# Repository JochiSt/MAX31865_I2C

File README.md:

# MAX31865_I2C
SPI to I2C bridge fo iInterfacing the MAX31865 via I2C

# Board / Hardware
The hardware has the same size as the Adafriut MAX31865 module. Also the SPI
connection is at the same position. This allows mounting the module on the back
of the MAX31865 module.

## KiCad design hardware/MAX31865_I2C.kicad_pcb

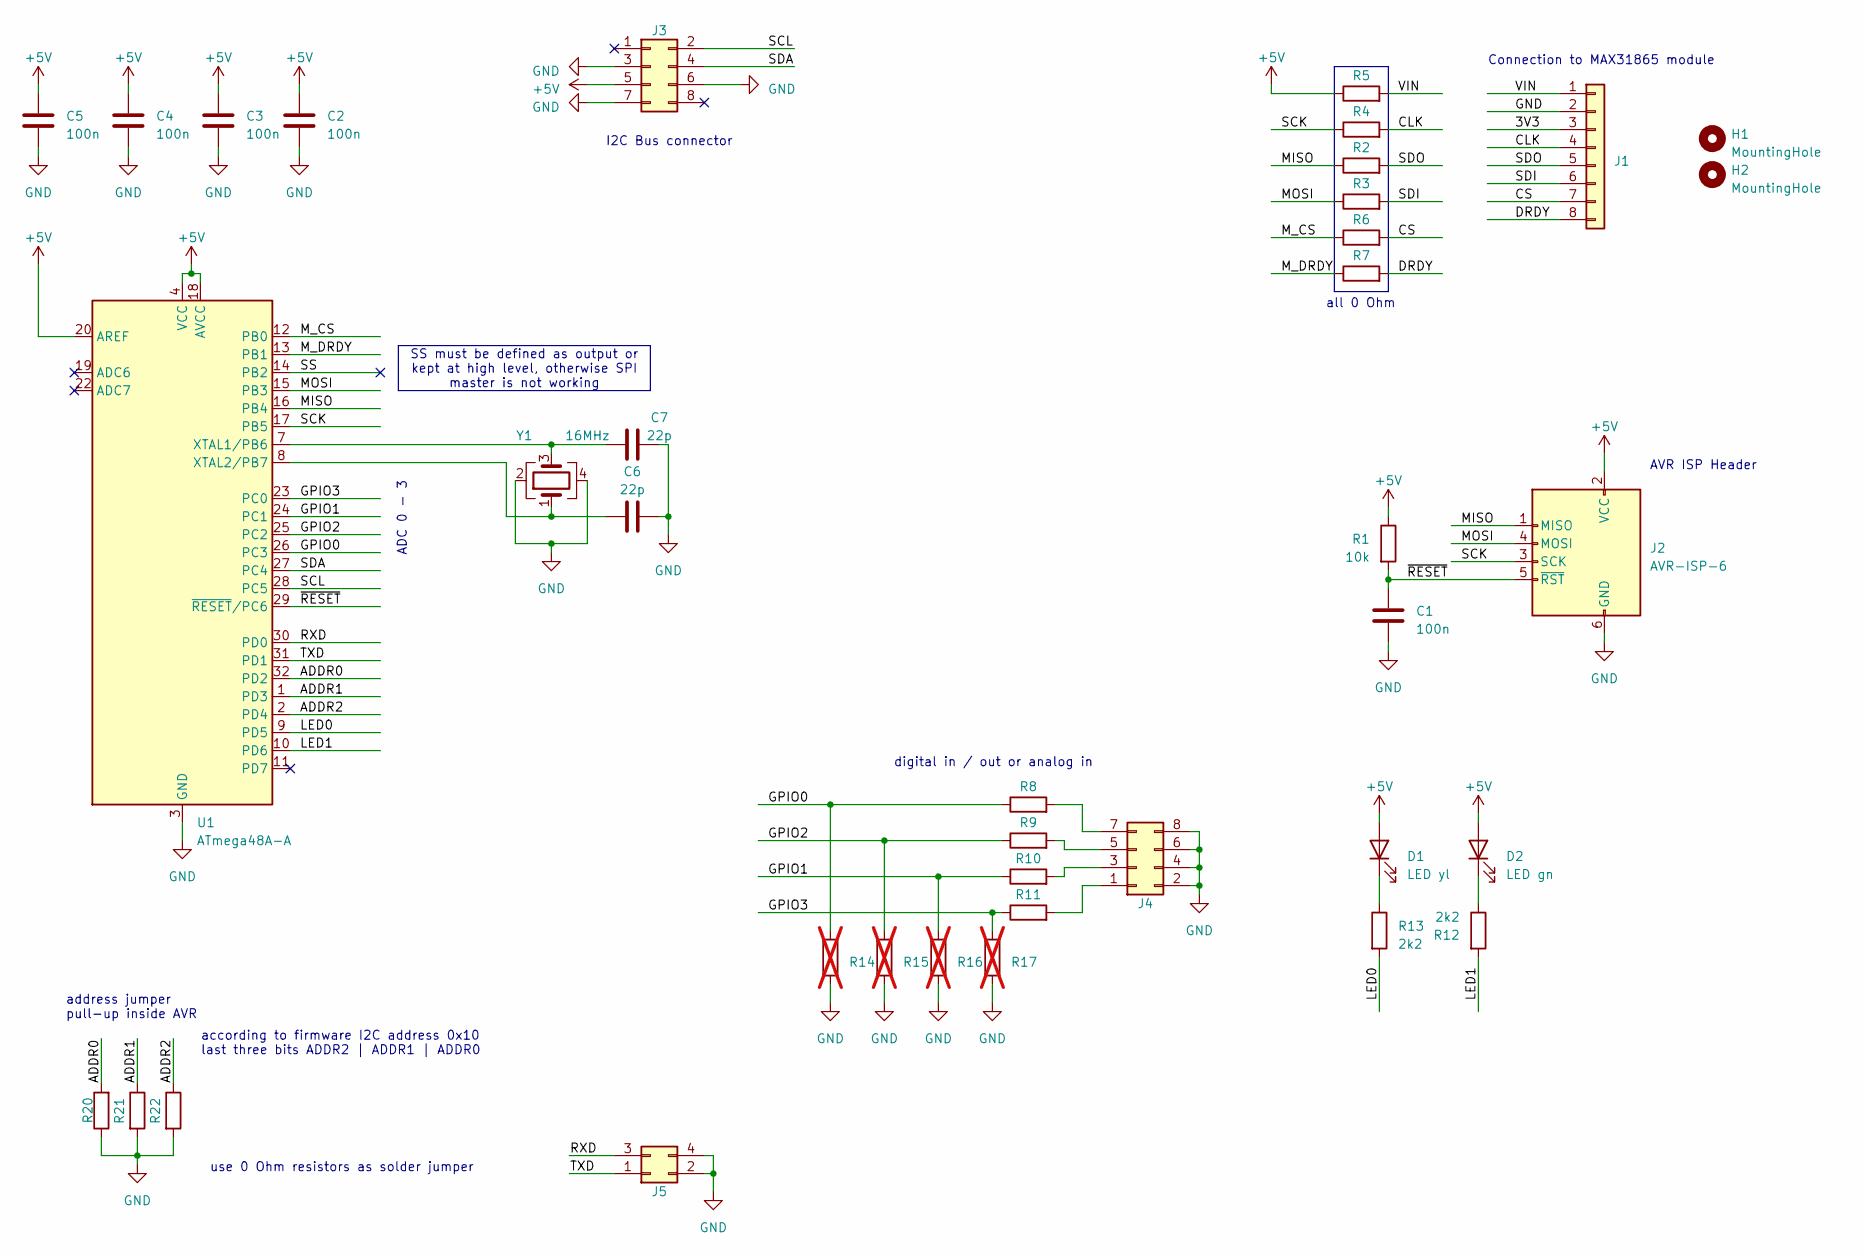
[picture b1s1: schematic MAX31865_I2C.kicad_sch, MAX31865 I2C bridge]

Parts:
C1, C2, C3, C4, C5: 100n; C_0603_1608Metric
C6, C7: 22p; C_0603_1608Metric
D1: LED yl; LED_0603_1608Metric
D2: LED gn; LED_0603_1608Metric
H1, H2: MountingHole; MountingHole_2.7mm
J1: Conn_01x08; PinSocket_1x08_P2.54mm_Vertical
J2: AVR-ISP-6; PinHeader_2x03_P2.54mm_Edge
J3, J4: Conn_02x04_Odd_Even; PinHeader_2x04_P2.54mm_Edge
J5: Conn_02x02_Odd_Even; PinHeader_2x02_P2.54mm_Edge
R1: 10k; R_0603_1608Metric
R2, R3, R4, R5, R6, R7, R8, R9, R10, R11: 0; R_0603_1608Metric
R12, R13: 2k2; R_0603_1608Metric
R14, R15, R16, R17: R_0603_1608Metric; not fitted
R20, R21, R22: R_0603_1608Metric
U1: ATmega48A-A; TQFP-32_7x7mm_P0.8mm
Y1: 16MHz; Crystal_SMD_EuroQuartz_MQ-4Pin_7.0x5.0mm

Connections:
+5V: C2.1, C3.1, C4.1, C5.1, D1.2 (A), D2.2 (A), J2.2 (VCC), J3.5, R1.1, R5.1, U1.4 (VCC), U1.6 (VCC), U1.18 (AVCC), U1.20 (AREF)
/3V3: J1.3
/ADDR0: R20.2, U1.32 (PD2)
/ADDR1: R21.1, U1.1 (PD3)
/ADDR2: R22.1, U1.2 (PD4)
/CLK: J1.4, R4.2
/CS: J1.7, R6.2
/DRDY: J1.8, R7.2
/GPIO0: R8.1, R14.2, U1.26 (PC3)
/GPIO1: R10.1, R16.2, U1.24 (PC1)
/GPIO2: R9.1, R15.2, U1.25 (PC2)
/GPIO3: R11.1, R17.2, U1.23 (PC0)
/LED0: R13.2, U1.9 (PD5)
/LED1: R12.2, U1.10 (PD6)
/MISO: J2.1 (MISO), R2.1, U1.16 (PB4)
/MOSI: J2.4 (MOSI), R3.1, U1.15 (PB3)
/M_CS: R6.1, U1.12 (PB0)
/M_DRDY: R7.1, U1.13 (PB1)
/RXD: J5.3, U1.30 (PD0)
/SCK: J2.3 (SCK), R4.1, U1.17 (PB5)
/SCL: J3.2, U1.28 (PC5)
/SDA: J3.4, U1.27 (PC4)
/SDI: J1.6, R3.2
/SDO: J1.5, R2.2
/SS: U1.14 (PB2)
/TXD: J5.1, U1.31 (PD1)
/VIN: J1.1, R5.2
/~RESET: C1.1, J2.5 (~RST), R1.2, U1.29 (~RESET/PC6)
GND: C1.2, C2.2, C3.2, C4.2, C5.2, C6.2, C7.2, J1.2, J2.6 (GND), J3.3, J3.6, J3.7, J4.2, J4.4, J4.6, J4.8, J5.2, J5.4, R14.1, R15.1, R16.1, R17.1, R20.1, R21.2, R22.2, U1.3 (GND), U1.5 (GND), U1.21 (GND), Y1.2, Y1.4
unnamed: D1.1 (K), R13.1
unnamed: D2.1 (K), R12.1
unnamed: J4.1, R11.2
unnamed: J4.3, R10.2
unnamed: J4.5, R9.2
unnamed: J4.7, R8.2
unnamed: C7.1, U1.7 (XTAL1/PB6), Y1.3
unnamed: C6.1, U1.8 (XTAL2/PB7), Y1.1

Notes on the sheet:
SS must be defined as output or kept at high level, otherwise SPI master is not working
ADC 0 - 3
according to firmware I2C address 0x10 last three bits ADDR2 | ADDR1 | ADDR0
AVR ISP Header
Connection to MAX31865 module
digital in / out or analog in
address jumper pull-up inside AVR
I2C Bus connector
all 0 Ohm
use 0 Ohm resistors as solder jumper

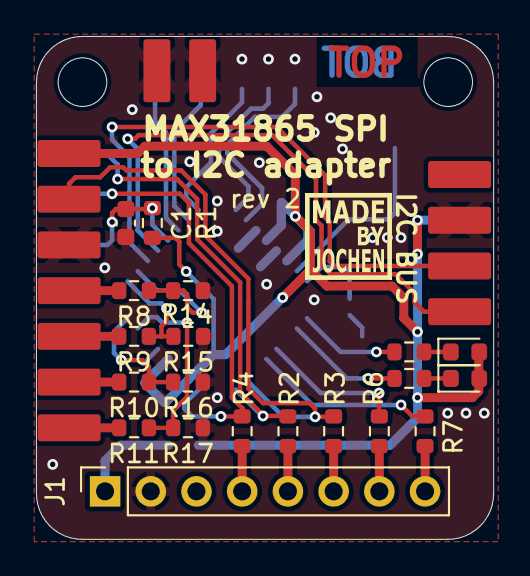
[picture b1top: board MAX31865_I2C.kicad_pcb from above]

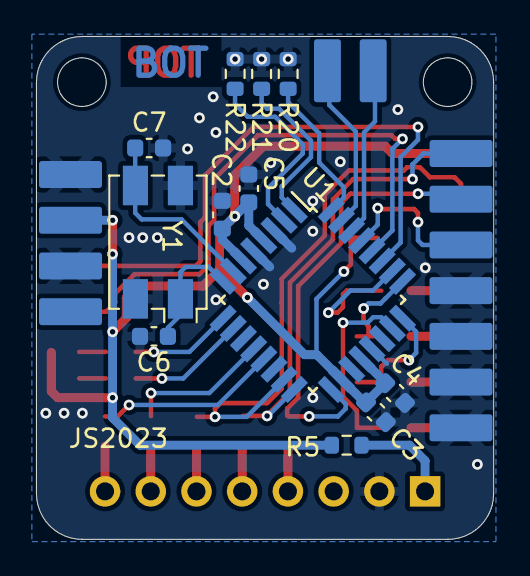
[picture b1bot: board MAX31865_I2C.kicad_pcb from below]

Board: 2 copper layers, 25.4 x 27.9 mm, 38 parts (13 on the bottom side), 35 nets.

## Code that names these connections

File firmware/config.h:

/**
 * Store some configuration values
 */

#ifndef CONFIG_H
#define CONFIG_H

#define LED0    D,5     // access via I2C
#define LED1    D,6     // keep alive signal

#define ADDR0   D,2
#define ADDR1   D,3
#define ADDR2   D,4

#define GPIO0   C,3
#define GPIO1   C,1
#define GPIO2   C,2
#define GPIO3   C,0

#define BAUDRATE 9600

#endif /* CONFIG_H */

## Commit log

2023-02-05 ignore *.hex
2023-02-05 added firmware template from old projects
2023-02-05 added EmBitz project files
2023-02-05 added MAX31865 AVR as submodule
2023-02-05 Update MAX31865_AVR
2023-02-05 include all object files in list
2023-02-05 added two register for reading the RTD value
2023-02-05 updated addr pins
    since the MAX31865 is using the B port -> move address pins to C
2023-02-05 include the MAX31865
2023-02-05 fixed old style definition
2023-02-06 removed safemode option, because it is no longer supported
2023-02-06 added simple I2C scanner
2023-02-06 ignore spyder project
2023-02-06 set i2c_scan baudrate to 100
2023-02-06 fixed callbacks and pointer types
2023-02-06 read and write function are now properly handled via callbacks
2023-02-06 replaced old comment by new documentation
2023-02-06 set the callbacks
2023-02-06 added ISR for TIMER0
2023-02-06 moved I2C_SIZE_READONLY label to right position
2023-02-07 include debugging via usart
2023-02-07 added some debug output
2023-02-07 added python script for testing the I2C readout
2023-02-07 include MAX31865 in the timer loop
2023-02-07 put MAX31865_I2C functions in class
    easier to use and much more structured
2023-02-07 needed some intermediate variables
2023-02-07 ensure, that the enum starts at zero
2023-02-07 added conversion from ADC counts to resistance
2023-02-07 do not check against faults before each readout
    this spoiled the readout of the RTD
2023-02-07 include the MAX CONFIG in the I2C memory map
2023-02-07 added some comments
2023-02-07 updated submodule
2023-02-07 started KiCAD project for building a small PCB
2023-02-08 started hardware development
2023-02-08 ignore auto saved files
2023-02-08 added rough sketch of the adapter PCB
2023-02-08 added caps for crystal
2023-02-08 connected CS and DRDY of MAX31865 module
2023-02-09 added footprint for 2x2 pin header edge mount
2023-02-09 made courtyard closed shape
2023-02-09 added KiCAD templates submodule
2023-02-09 added template for schematic and cleaned PCB a tiny bit
2023-02-09 updated measurements
2023-02-09 updated EmBitz Project and ignore layout
2023-02-09 ignore doxygen documentation
2023-02-09 added Doxyfile for generating the documentation
2023-02-10 added 3D renderings
2023-02-10 include the 3D rendered images
2023-02-10 updated inclusion of images
2023-02-11 ERC and DRC clean
2023-02-11 added comments for inputs / output connections
2023-02-11 added some comments to schematic
2023-02-11 added further comments
2023-02-11 added MadeByJochen logo
2023-02-11 added Revision Text Variable to PCB
2023-02-11 ignore pycache
2023-02-11 added class to generate some enum equivalent
2023-02-11 added script to generate a pythonic register map from the C enum
2023-02-11 use standart python enum
2023-02-11 added small test for generated register map
2023-02-11 tweaked output formatting
2023-02-11 added some header to output file
2023-02-11 added generated register map
2023-02-11 changed name of status counter register
2023-02-11 use register map in MAX31865_I2C class
2023-02-11 fixed typo
2023-02-12 register addresses have been replaced by I2C map
2023-02-12 store R_REF as class variable, so this can be used for PT1000 and PT100
2023-02-12 updated pin mapping to match latest PCB revision
2023-02-13 removed FaultError IF clauses
2023-02-13 use configuration from EEPROM
2023-02-14 added some docstrings
2023-02-17 a bit of code cleanup
2023-02-17 tiny update to schematic and pcb
    updated to KiCAD v7 release version
    updated version in PCB
    updated LED colors
2023-02-17 updated meaning for LED
2023-02-17 added IBOM configuration
2023-03-06 include LED port initialisation
2023-03-06 added support for ATmega88P and 48P
2023-03-06 changed target to MEGA48P
2023-03-06 added comment to MAX31865 configuration
2023-03-06 use reg_addr as name for register address derived from register map
2023-03-06 removed User.1 to User.9
2023-03-06 added LED color to fabrication
2023-03-06 added pinout to comment layer
2023-03-06 some minor updates to PCB
2023-03-06 BUGFIX: fixed initial layers for odd and even
    They have been swapped.
2023-03-06 fixed edge connectors for ISP
2023-03-06 GPIO input section redesign
    Satisfies now the inner Monk
2023-03-06 updated register map test
2023-08-01 added submodule and basic support for 1wire sensors
2023-08-01 changed device to ATMEGA88 for more memory (which is not really needed)
2023-10-04 updated fuses to match Atmega88
2023-10-04 added include of <var/interrupt.h> removed return 0 from void function
2023-10-04 removed old style warning
2023-10-05 use FUSE EESAVE to prevent EEPROM from being deleted
2023-10-05 use compile time flag for enable / disable DEBUG UART
2023-10-05 removed not needed include path
2023-10-05 added commands to generate EEPROM content and to program it
2023-10-05 removed redundant targets
2023-10-05 included BoardID as environmental variable (or default)
2024-01-17 added note about I2C address to schematic
2024-01-17 ignore lck files
